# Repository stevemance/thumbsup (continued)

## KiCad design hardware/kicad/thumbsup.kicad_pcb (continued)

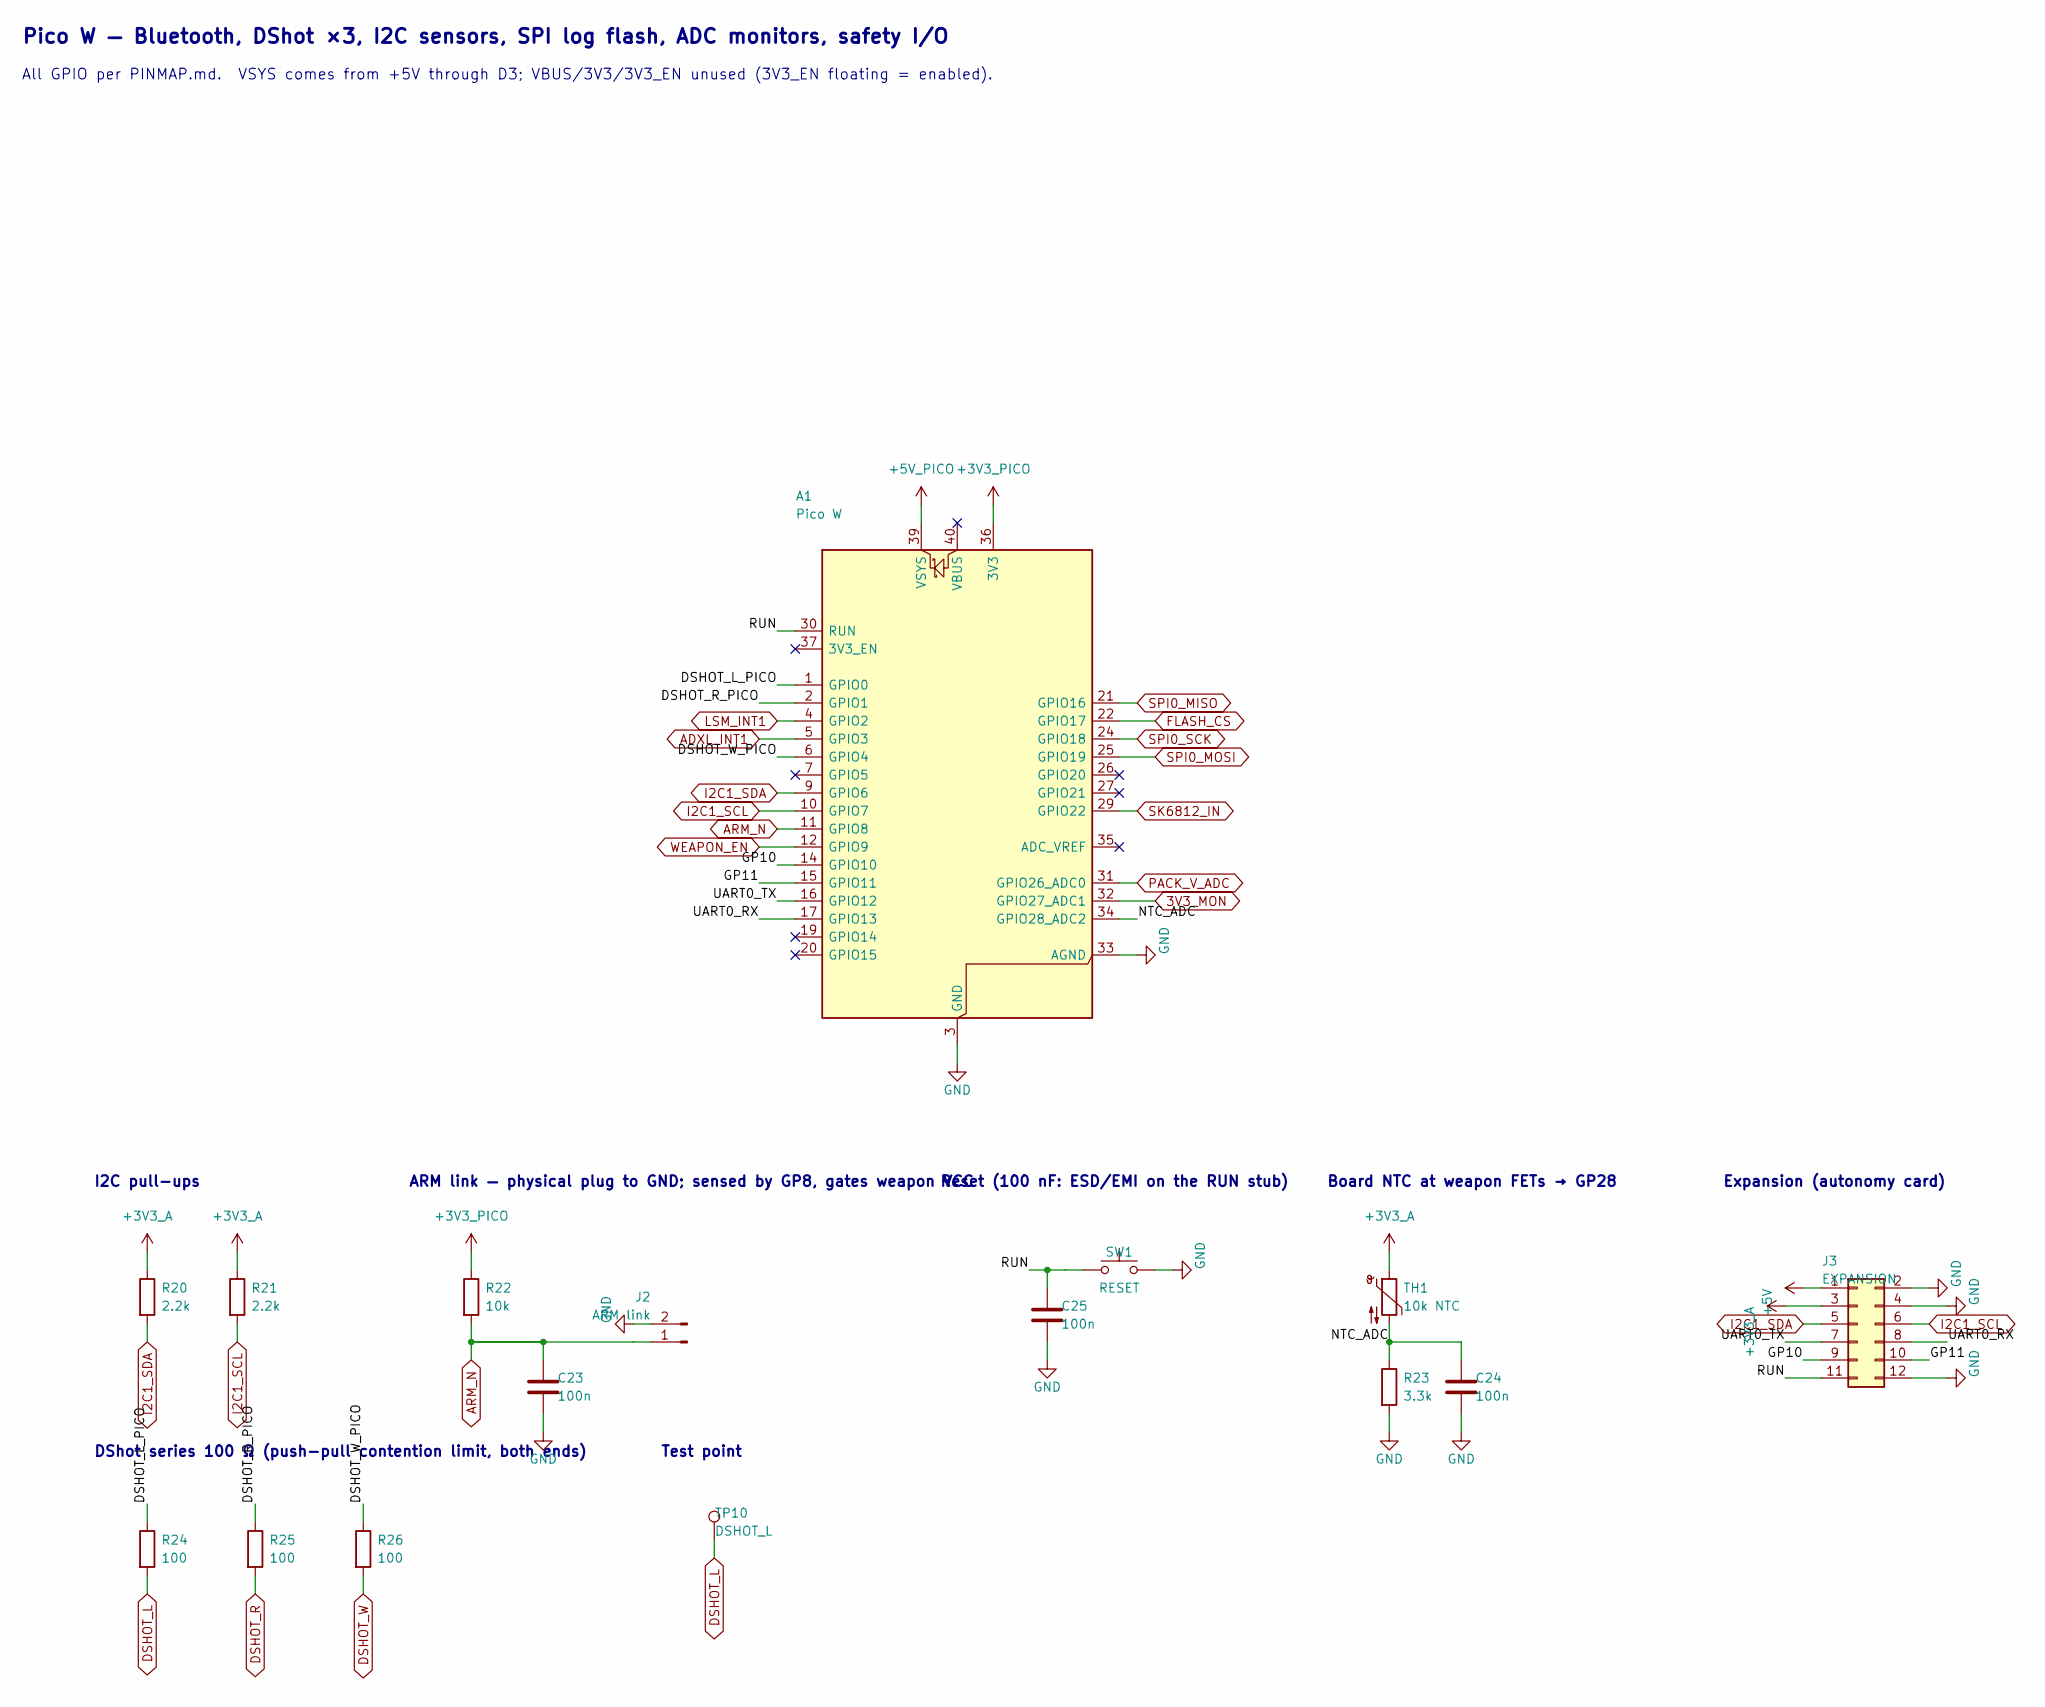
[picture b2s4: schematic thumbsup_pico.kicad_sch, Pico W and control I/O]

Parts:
A1: Pico W; RaspberryPi_Pico_W_SMD_HandSolder
C23, C24, C25: 100n; C_0402_1005Metric; LCSC C1525
J2: ARM link; PinHeader_1x02_P2.54mm_Vertical
J3: EXPANSION; PinHeader_2x06_P2.54mm_Vertical
R20, R21: 2.2k; R_0402_1005Metric; LCSC C25879
R22: 10k; R_0402_1005Metric; LCSC C25744
R23: 3.3k; R_0402_1005Metric; LCSC C25890
R24, R25, R26: 100; R_0402_1005Metric; LCSC C25076
SW1: RESET; SW_Push_1P1T_XKB_TS-1187A; LCSC C318884
TH1: 10k NTC; R_0603_1608Metric; LCSC C13564
TP10: DSHOT_L; TestPoint_Pad_D1.5mm

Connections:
3V3_MON: A1.32 (GPIO27_ADC1); also elsewhere on the board
+3V3_A: J3.3, R20.1, R21.1, TH1.1; also elsewhere on the board
+3V3_PICO: A1.36 (3V3), R22.1
+5V: J3.1; also elsewhere on the board
+5V_PICO: A1.39 (VSYS); also elsewhere on the board
/Pico W and control I/O/DSHOT_L_PICO: A1.1 (GPIO0), R24.1
/Pico W and control I/O/DSHOT_R_PICO: A1.2 (GPIO1), R25.1
/Pico W and control I/O/DSHOT_W_PICO: A1.6 (GPIO4), R26.1
/Pico W and control I/O/GP10: A1.14 (GPIO10), J3.9
/Pico W and control I/O/GP11: A1.15 (GPIO11), J3.10
/Pico W and control I/O/NTC_ADC: A1.34 (GPIO28_ADC2), C24.1, R23.1, TH1.2
/Pico W and control I/O/RUN: A1.30 (RUN), C25.1, J3.11, SW1.1
/Pico W and control I/O/UART0_RX: A1.17 (GPIO13), J3.8
/Pico W and control I/O/UART0_TX: A1.16 (GPIO12), J3.7
ADXL_INT1: A1.5 (GPIO3); also elsewhere on the board
ARM_N: A1.11 (GPIO8), C23.1, J2.1, R22.2; also elsewhere on the board
DSHOT_L: R24.2, TP10.1; also elsewhere on the board
DSHOT_R: R25.2; also elsewhere on the board
DSHOT_W: R26.2; also elsewhere on the board
FLASH_CS: A1.22 (GPIO17); also elsewhere on the board
GND: A1.3 (GND), A1.8 (GND), A1.13 (GND), A1.18 (GND), A1.23 (GND), A1.28 (GND), A1.33 (AGND), A1.38 (GND), C23.2, C24.2, C25.2, J2.2, J3.2, J3.4, J3.12, R23.2, SW1.2; also elsewhere on the board
I2C1_SCL: A1.10 (GPIO7), J3.6, R21.2; also elsewhere on the board
I2C1_SDA: A1.9 (GPIO6), J3.5, R20.2; also elsewhere on the board
LSM_INT1: A1.4 (GPIO2); also elsewhere on the board
PACK_V_ADC: A1.31 (GPIO26_ADC0); also elsewhere on the board
SK6812_IN: A1.29 (GPIO22); also elsewhere on the board
SPI0_MISO: A1.21 (GPIO16); also elsewhere on the board
SPI0_MOSI: A1.25 (GPIO19); also elsewhere on the board
SPI0_SCK: A1.24 (GPIO18); also elsewhere on the board
WEAPON_EN: A1.12 (GPIO9); also elsewhere on the board

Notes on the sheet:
Pico W — Bluetooth, DShot ×3, I2C sensors, SPI log flash, ADC monitors, safety I/O
All GPIO per PINMAP.md. VSYS comes from +5V through D3; VBUS/3V3/3V3_EN unused (3V3_EN floating = enabled).
I2C pull-ups
ARM link — physical plug to GND; sensed by GP8, gates weapon VCC
Reset (100 nF: ESD/EMI on the RUN stub)
DShot series 100 Ω (push-pull contention limit, both ends)
Test point
Board NTC at weapon FETs → GP28
Expansion (autonomy card)

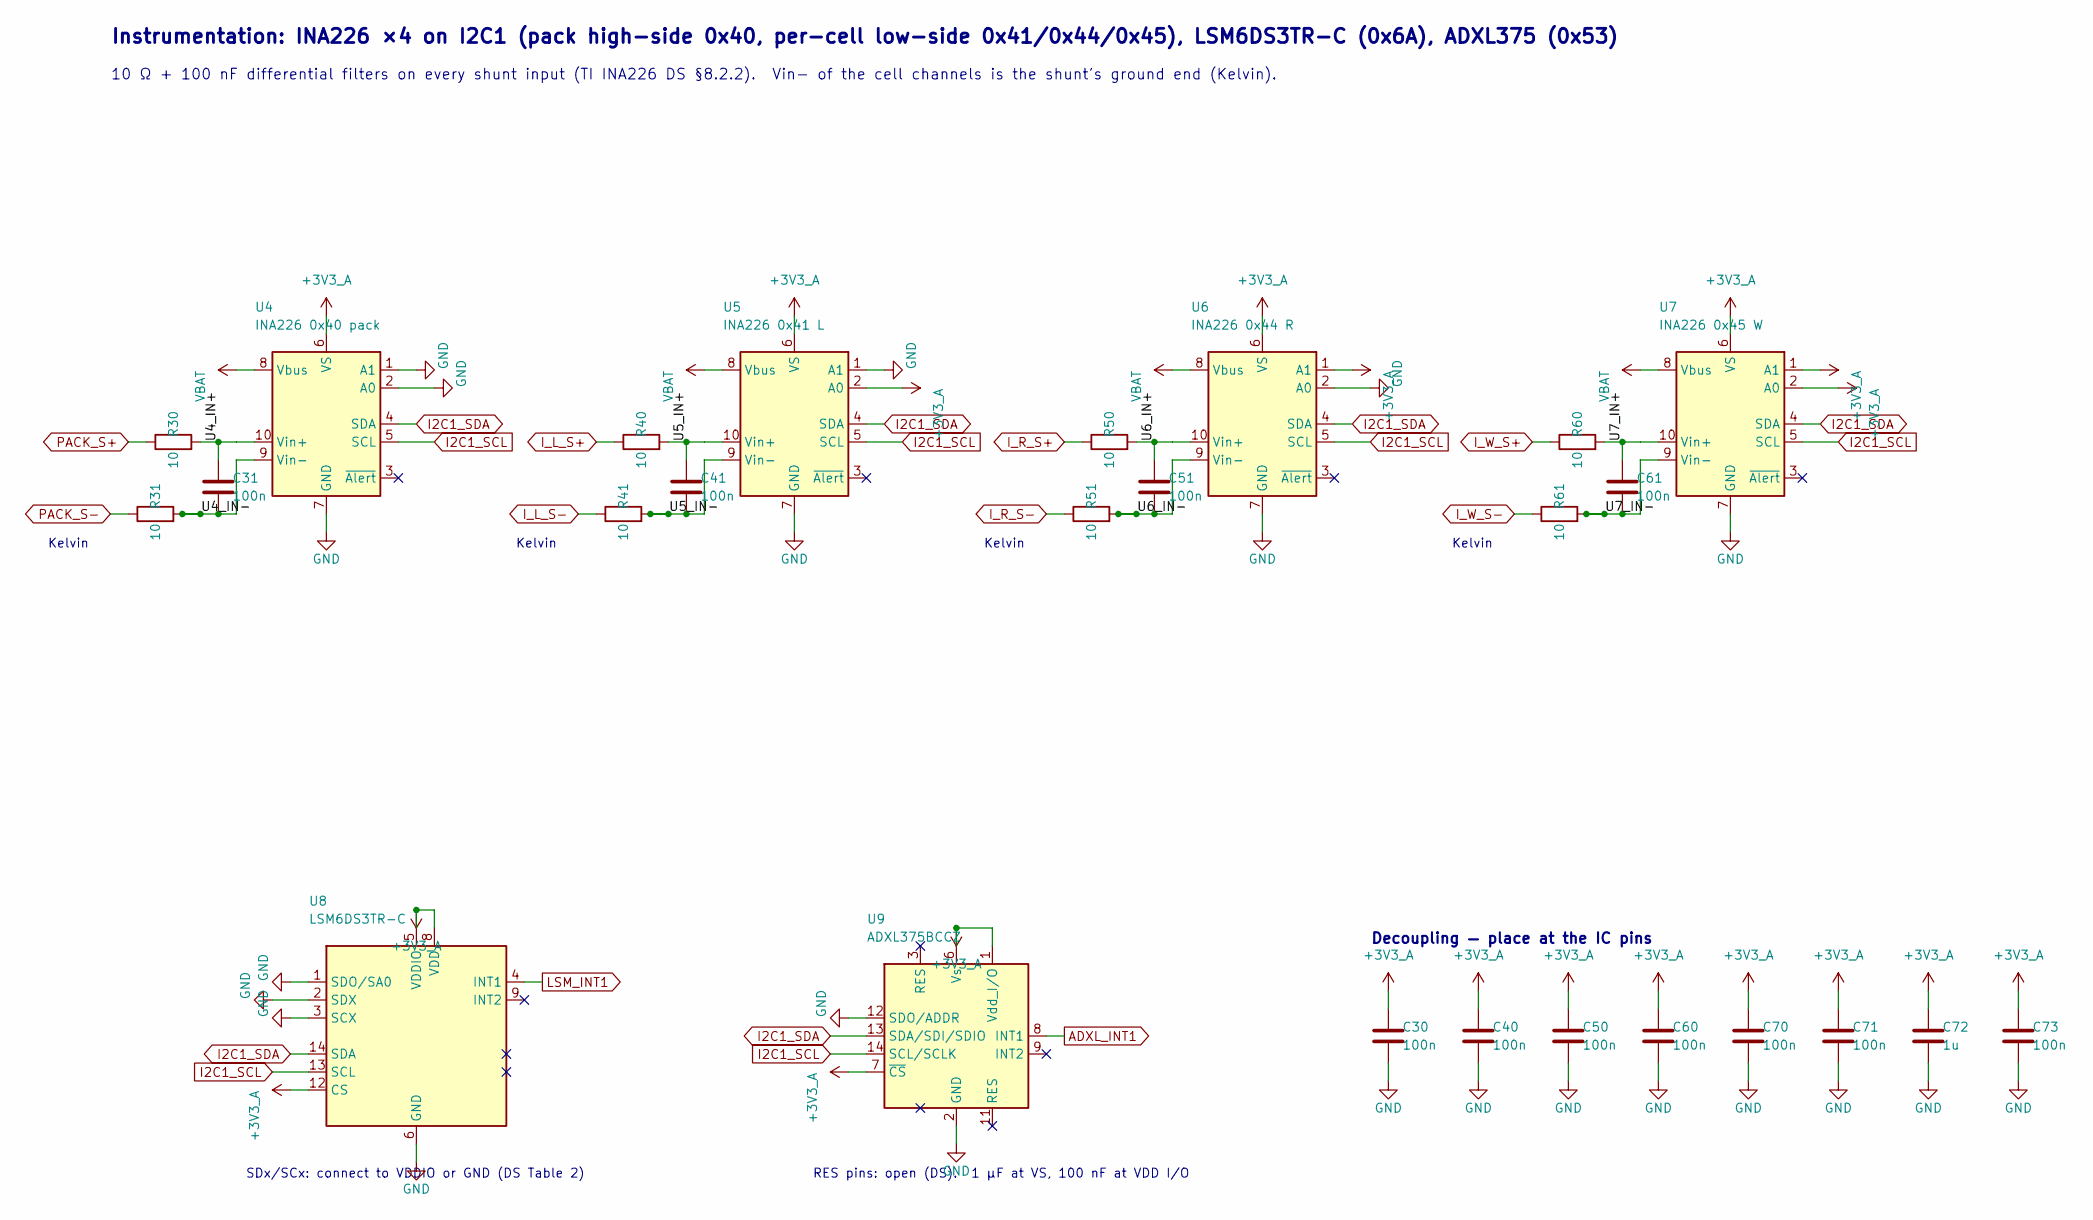
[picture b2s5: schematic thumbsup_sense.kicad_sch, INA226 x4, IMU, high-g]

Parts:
C30, C31, C40, C41, C50, C51, C60, C61, C70, C71, C73: 100n; C_0402_1005Metric; LCSC C1525
C72: 1u; C_0402_1005Metric; LCSC C52923
R30, R31, R40, R41, R50, R51, R60, R61: 10; R_0402_1005Metric; LCSC C25077
U4: INA226 0x40 pack; MSOP-10_3x3mm_P0.5mm; LCSC C49851
U5: INA226 0x41 L; MSOP-10_3x3mm_P0.5mm; LCSC C49851
U6: INA226 0x44 R; MSOP-10_3x3mm_P0.5mm; LCSC C49851
U7: INA226 0x45 W; MSOP-10_3x3mm_P0.5mm; LCSC C49851
U8: LSM6DS3TR-C; LGA-14_3x2.5mm_P0.5mm_LayoutBorder3x4y; LCSC C967633
U9: ADXL375BCCZ; LGA-14_3x5mm_P0.8mm_LayoutBorder1x6y; LCSC C579466

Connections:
+3V3_A: C30.1, C40.1, C50.1, C60.1, C70.1, C71.1, C72.1, C73.1, U4.6 (VS), U5.2 (A0), U5.6 (VS), U6.1 (A1), U6.6 (VS), U7.1 (A1), U7.2 (A0), U7.6 (VS), U8.5 (VDDIO), U8.8 (VDD), U8.12 (CS), U9.1 (Vdd_I/O), U9.6 (Vs), U9.7 (~CS); also elsewhere on the board
/INA226 x4, IMU, high-g/U4_IN+: C31.1, R30.2, U4.10 (Vin+)
/INA226 x4, IMU, high-g/U4_IN-: C31.2, R31.2, U4.9 (Vin-)
/INA226 x4, IMU, high-g/U5_IN+: C41.1, R40.2, U5.10 (Vin+)
/INA226 x4, IMU, high-g/U5_IN-: C41.2, R41.2, U5.9 (Vin-)
/INA226 x4, IMU, high-g/U6_IN+: C51.1, R50.2, U6.10 (Vin+)
/INA226 x4, IMU, high-g/U6_IN-: C51.2, R51.2, U6.9 (Vin-)
/INA226 x4, IMU, high-g/U7_IN+: C61.1, R60.2, U7.10 (Vin+)
/INA226 x4, IMU, high-g/U7_IN-: C61.2, R61.2, U7.9 (Vin-)
ADXL_INT1: U9.8 (INT1); also elsewhere on the board
GND: C30.2, C40.2, C50.2, C60.2, C70.2, C71.2, C72.2, C73.2, U4.1 (A1), U4.2 (A0), U4.7 (GND), U5.1 (A1), U5.7 (GND), U6.2 (A0), U6.7 (GND), U7.7 (GND), U8.1 (SDO/SA0), U8.2 (SDX), U8.3 (SCX), U8.6 (GND), U8.7 (GND), U9.2 (GND), U9.4 (GND), U9.5 (GND), U9.12 (SDO/ADDR); also elsewhere on the board
I2C1_SCL: U4.5 (SCL), U5.5 (SCL), U6.5 (SCL), U7.5 (SCL), U8.13 (SCL), U9.14 (SCL/SCLK); also elsewhere on the board
I2C1_SDA: U4.4 (SDA), U5.4 (SDA), U6.4 (SDA), U7.4 (SDA), U8.14 (SDA), U9.13 (SDA/SDI/SDIO); also elsewhere on the board
I_L_S+: R40.1; also elsewhere on the board
I_L_S-: R41.1; also elsewhere on the board
I_R_S+: R50.1; also elsewhere on the board
I_R_S-: R51.1; also elsewhere on the board
I_W_S+: R60.1; also elsewhere on the board
I_W_S-: R61.1; also elsewhere on the board
LSM_INT1: U8.4 (INT1); also elsewhere on the board
PACK_S+: R30.1; also elsewhere on the board
PACK_S-: R31.1; also elsewhere on the board
VBAT: U4.8 (Vbus), U5.8 (Vbus), U6.8 (Vbus), U7.8 (Vbus); also elsewhere on the board

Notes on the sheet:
Instrumentation: INA226 ×4 on I2C1 (pack high-side 0x40, per-cell low-side 0x41/0x44/0x45), LSM6DS3TR-C (0x6A), ADXL375 (0x53)
10 Ω + 100 nF differential filters on every shunt input (TI INA226 DS §8.2.2). Vin− of the cell channels is the shunt's ground end (Kelvin).
Kelvin
SDx/SCx: connect to VDDIO or GND (DS Table 2)
RES pins: open (DS). 1 µF at VS, 100 nF at VDD I/O
Decoupling — place at the IC pins

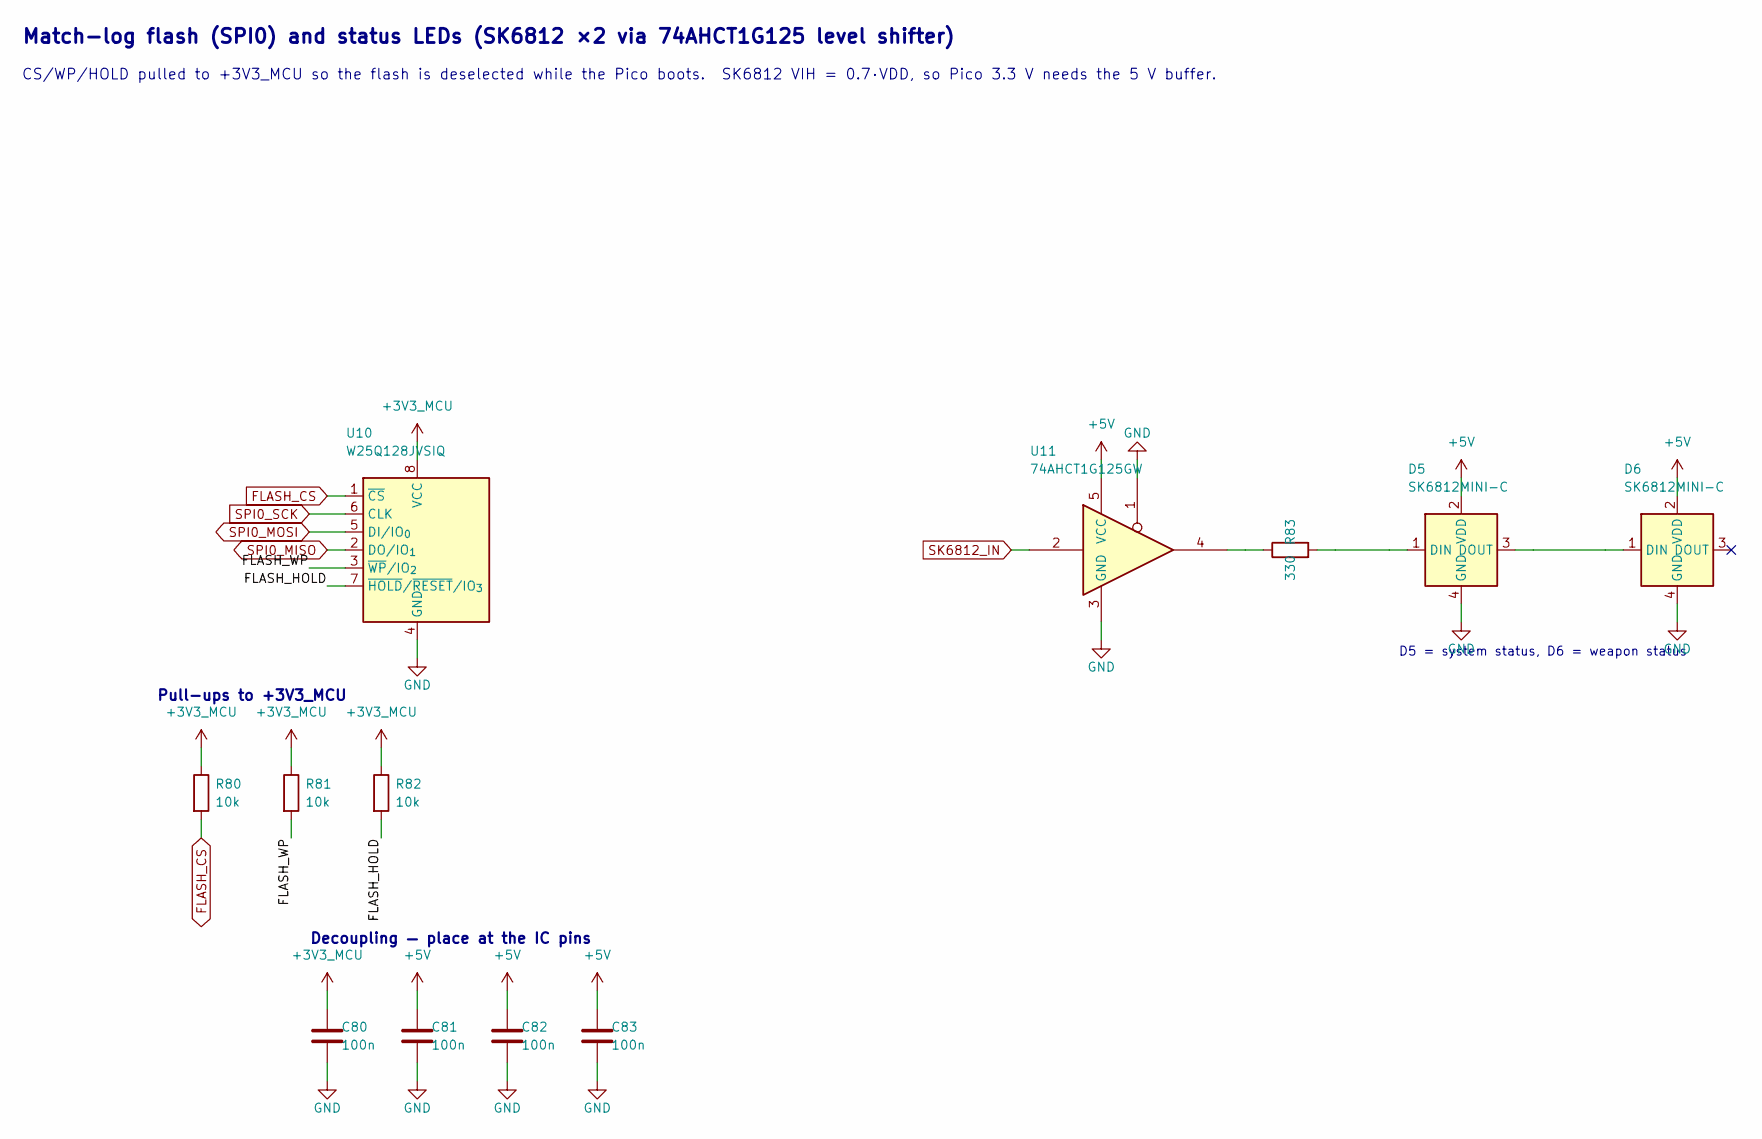
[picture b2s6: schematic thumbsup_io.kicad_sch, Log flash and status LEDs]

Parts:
C80, C81, C82, C83: 100n; C_0402_1005Metric; LCSC C1525
D5, D6: SK6812MINI-C; LED_SK6812MINI_PLCC4_3.5x3.5mm_P1.75mm; LCSC C7423117
R80, R81, R82: 10k; R_0402_1005Metric; LCSC C25744
R83: 330; R_0402_1005Metric; LCSC C25104
U10: W25Q128JVSIQ; SOIC-8_5.3x5.3mm_P1.27mm; LCSC C97521
U11: 74AHCT1G125GW; SOT-353_SC-70-5; LCSC C52953352

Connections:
+3V3_MCU: C80.1, R80.1, R81.1, R82.1, U10.8 (VCC); also elsewhere on the board
+5V: C81.1, C82.1, C83.1, D5.2 (VDD), D6.2 (VDD), U11.5 (VCC); also elsewhere on the board
/Log flash and status LEDs/FLASH_HOLD: R82.2, U10.7 (~HOLD/~RESET/IO_{3})
/Log flash and status LEDs/FLASH_WP: R81.2, U10.3 (~WP/IO_{2})
FLASH_CS: R80.2, U10.1 (~CS); also elsewhere on the board
GND: C80.2, C81.2, C82.2, C83.2, D5.4 (GND), D6.4 (GND), U10.4 (GND), U11.1, U11.3 (GND); also elsewhere on the board
unnamed: D5.1 (DIN), R83.2
unnamed: D5.3 (DOUT), D6.1 (DIN)
unnamed: R83.1, U11.4
SK6812_IN: U11.2; also elsewhere on the board
SPI0_MISO: U10.2 (DO/IO_{1}); also elsewhere on the board
SPI0_MOSI: U10.5 (DI/IO_{0}); also elsewhere on the board
SPI0_SCK: U10.6 (CLK); also elsewhere on the board

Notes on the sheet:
Match-log flash (SPI0) and status LEDs (SK6812 ×2 via 74AHCT1G125 level shifter)
CS/WP/HOLD pulled to +3V3_MCU so the flash is deselected while the Pico boots. SK6812 VIH = 0.7·VDD, so Pico 3.3 V needs the 5 V buffer.
Pull-ups to +3V3_MCU
D5 = system status, D6 = weapon status
Decoupling — place at the IC pins

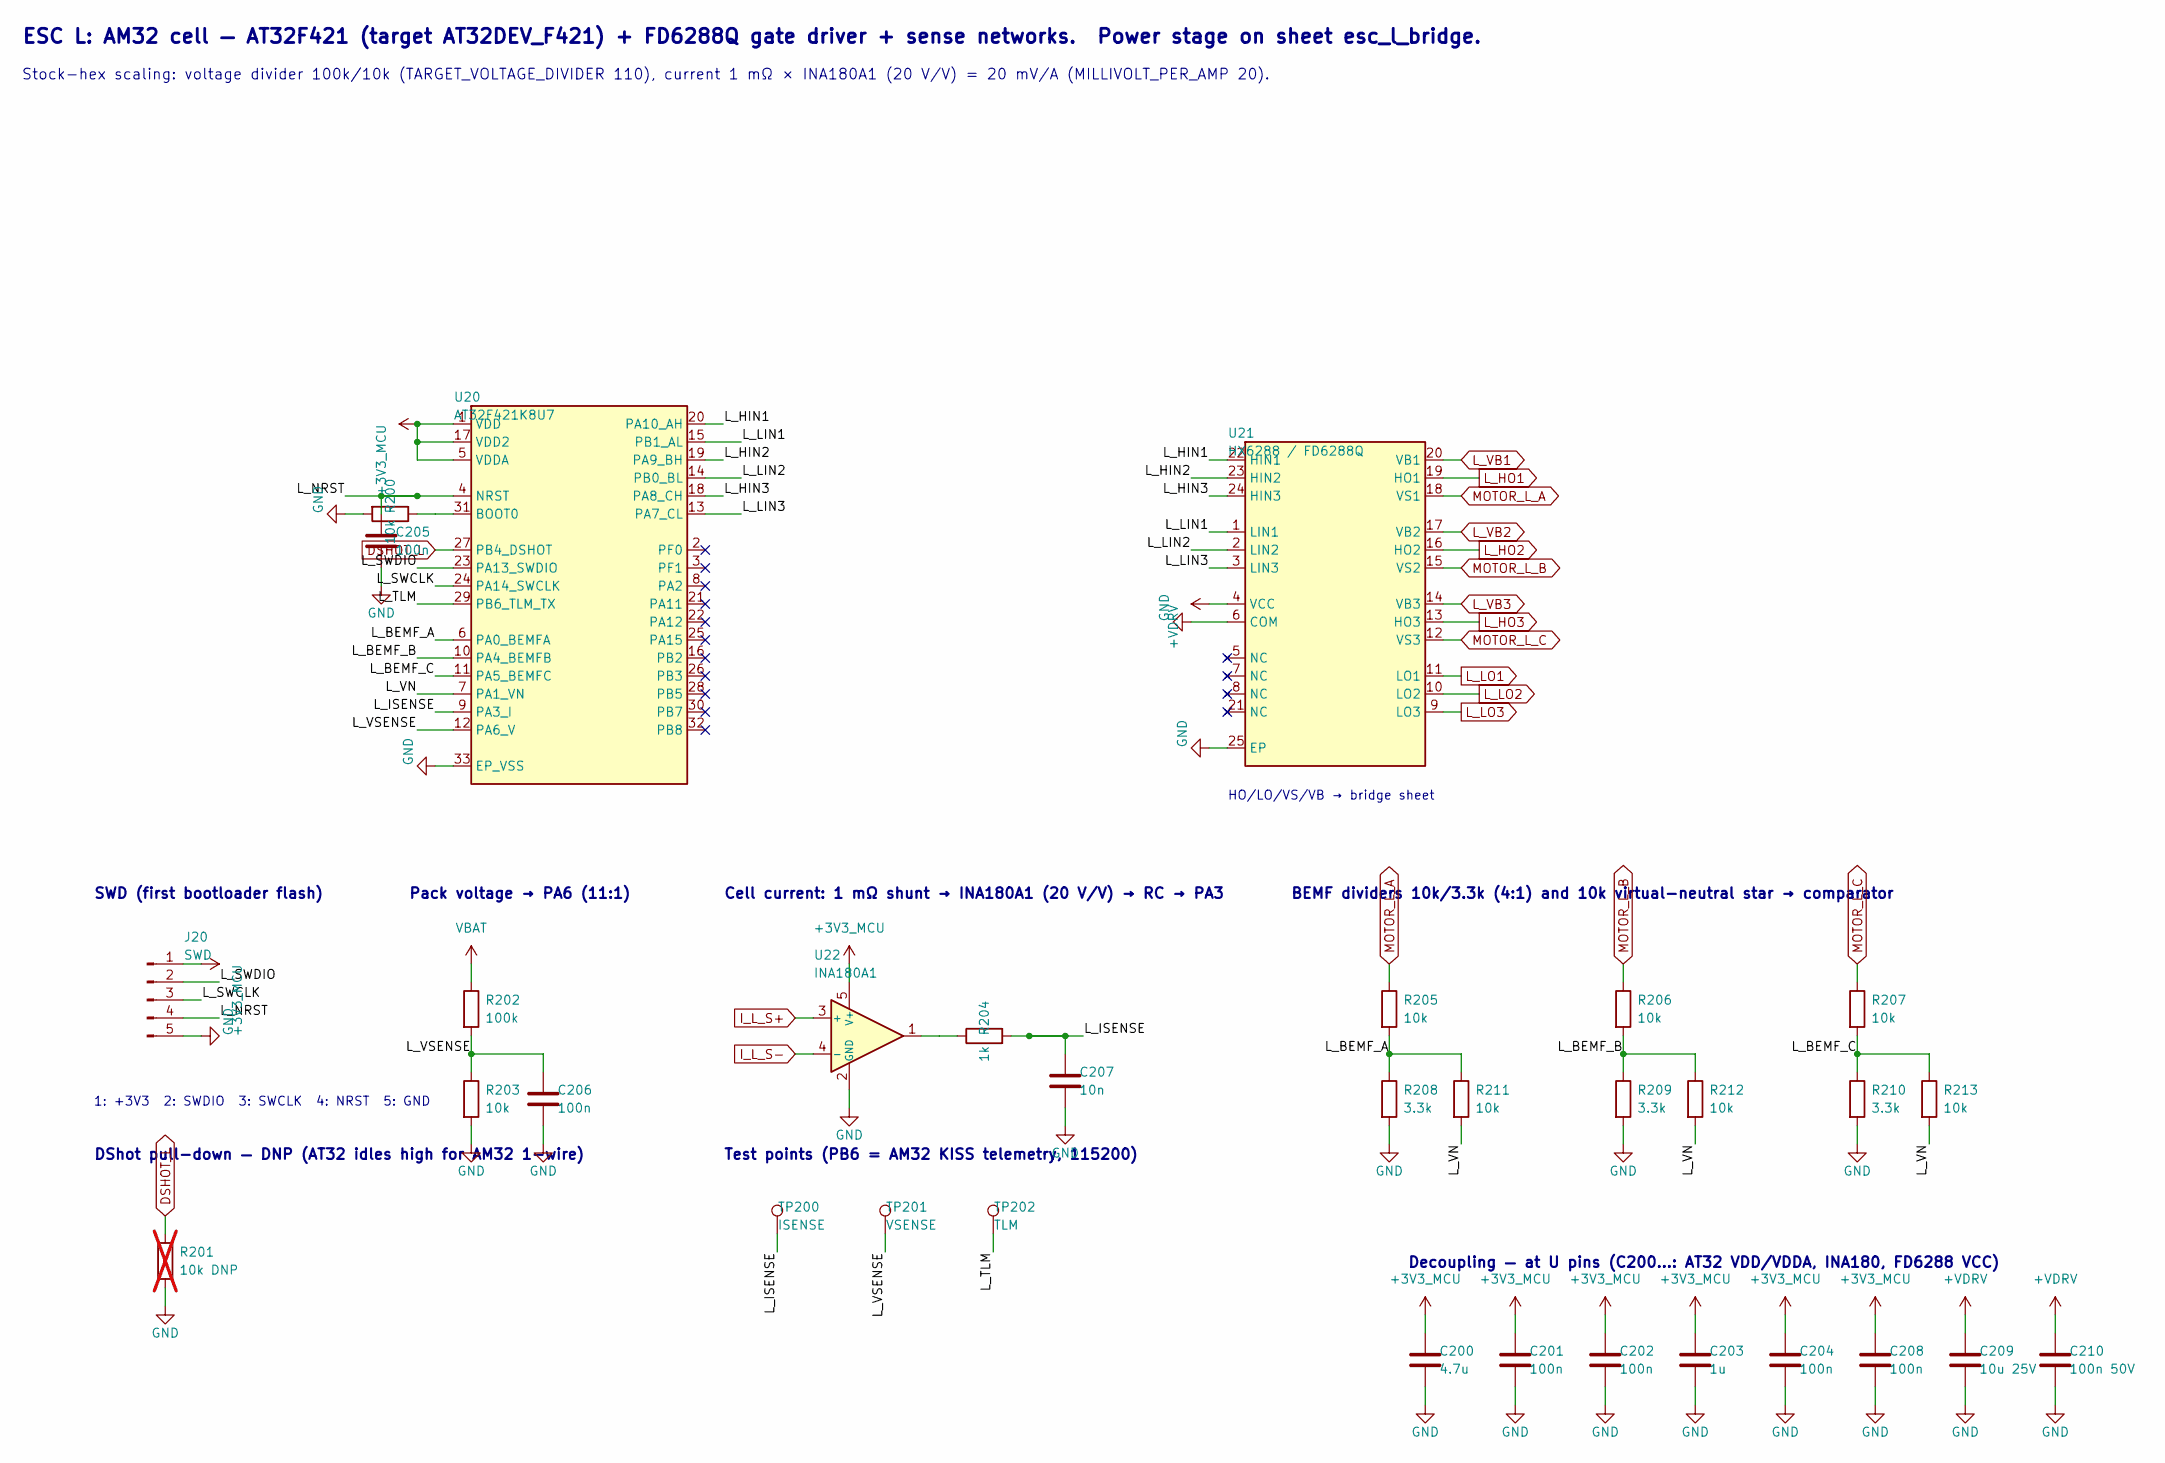
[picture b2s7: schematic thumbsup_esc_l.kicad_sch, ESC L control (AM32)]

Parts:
C200: 4.7u; C_0603_1608Metric; LCSC C19666
C201, C202, C204, C205, C206, C208: 100n; C_0402_1005Metric; LCSC C1525
C203: 1u; C_0402_1005Metric; LCSC C52923
C207: 10n; C_0402_1005Metric; LCSC C15195
C209: 10u 25V; C_0805_2012Metric; LCSC C15850
C210: 100n 50V; C_0603_1608Metric; LCSC C14663
J20: SWD; SWD_1x05_P1.27mm_Pads
R200, R203, R205, R206, R207, R211, R212, R213: 10k; R_0402_1005Metric; LCSC C25744
R201: 10k DNP; R_0402_1005Metric; LCSC C25744; not fitted
R202: 100k; R_0402_1005Metric; LCSC C25741
R204: 1k; R_0402_1005Metric; LCSC C11702
R208, R209, R210: 3.3k; R_0402_1005Metric; LCSC C25890
TP200: ISENSE; TestPoint_Pad_D1.5mm
TP201: VSENSE; TestPoint_Pad_D1.5mm
TP202: TLM; TestPoint_Pad_D1.5mm
U20: AT32F421K8U7; QFN-32-1EP_5x5mm_P0.5mm_EP3.3x3.3mm; LCSC C2965611
U21: HX6288 / FD6288Q; QFN-24-1EP_4x4mm_P0.5mm_EP2.7x2.7mm; LCSC C54423134
U22: INA180A1; SOT-23-5; LCSC C122228

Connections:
+3V3_MCU: C200.1, C201.1, C202.1, C203.1, C204.1, C208.1, J20.1, U20.1 (VDD), U20.5 (VDDA), U20.17 (VDD2), U22.5 (V+); also elsewhere on the board
+VDRV: C209.1, C210.1, U21.4 (VCC); also elsewhere on the board
/ESC L control (AM32)/L_BEMF_A: R205.2, R208.1, R211.1, U20.6 (PA0_BEMFA)
/ESC L control (AM32)/L_BEMF_B: R206.2, R209.1, R212.1, U20.10 (PA4_BEMFB)
/ESC L control (AM32)/L_BEMF_C: R207.2, R210.1, R213.1, U20.11 (PA5_BEMFC)
/ESC L control (AM32)/L_HIN1: U20.20 (PA10_AH), U21.22 (HIN1)
/ESC L control (AM32)/L_HIN2: U20.19 (PA9_BH), U21.23 (HIN2)
/ESC L control (AM32)/L_HIN3: U20.18 (PA8_CH), U21.24 (HIN3)
/ESC L control (AM32)/L_ISENSE: C207.1, R204.2, TP200.1, U20.9 (PA3_I)
/ESC L control (AM32)/L_LIN1: U20.15 (PB1_AL), U21.1 (LIN1)
/ESC L control (AM32)/L_LIN2: U20.14 (PB0_BL), U21.2 (LIN2)
/ESC L control (AM32)/L_LIN3: U20.13 (PA7_CL), U21.3 (LIN3)
/ESC L control (AM32)/L_NRST: C205.1, J20.4, U20.4 (NRST)
/ESC L control (AM32)/L_SWCLK: J20.3, U20.24 (PA14_SWCLK)
/ESC L control (AM32)/L_SWDIO: J20.2, U20.23 (PA13_SWDIO)
/ESC L control (AM32)/L_TLM: TP202.1, U20.29 (PB6_TLM_TX)
/ESC L control (AM32)/L_VN: R211.2, R212.2, R213.2, U20.7 (PA1_VN)
/ESC L control (AM32)/L_VSENSE: C206.1, R202.2, R203.1, TP201.1, U20.12 (PA6_V)
DSHOT_L: R201.1, U20.27 (PB4_DSHOT); also elsewhere on the board
GND: C200.2, C201.2, C202.2, C203.2, C204.2, C205.2, C206.2, C207.2, C208.2, C209.2, C210.2, J20.5, R200.2, R201.2, R203.2, R208.2, R209.2, R210.2, U20.33 (EP_VSS), U21.6 (COM), U21.25 (EP), U22.2 (GND); also elsewhere on the board
I_L_S+: U22.3 (+); also elsewhere on the board
I_L_S-: U22.4 (-); also elsewhere on the board
L_HO1: U21.19 (HO1); also elsewhere on the board
L_HO2: U21.16 (HO2); also elsewhere on the board
L_HO3: U21.13 (HO3); also elsewhere on the board
L_LO1: U21.11 (LO1); also elsewhere on the board
L_LO2: U21.10 (LO2); also elsewhere on the board
L_LO3: U21.9 (LO3); also elsewhere on the board
L_VB1: U21.20 (VB1); also elsewhere on the board
L_VB2: U21.17 (VB2); also elsewhere on the board
L_VB3: U21.14 (VB3); also elsewhere on the board
MOTOR_L_A: R205.1, U21.18 (VS1); also elsewhere on the board
MOTOR_L_B: R206.1, U21.15 (VS2); also elsewhere on the board
MOTOR_L_C: R207.1, U21.12 (VS3); also elsewhere on the board
unnamed: R204.1, U22.1
unnamed: R200.1, U20.31 (BOOT0)
VBAT: R202.1; also elsewhere on the board

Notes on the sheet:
ESC L: AM32 cell — AT32F421 (target AT32DEV_F421) + FD6288Q gate driver + sense networks. Power stage on sheet esc_l_bridge.
Stock-hex scaling: voltage divider 100k/10k (TARGET_VOLTAGE_DIVIDER 110), current 1 mΩ × INA180A1 (20 V/V) = 20 mV/A (MILLIVOLT_PER_AMP 20).
HO/LO/VS/VB → bridge sheet
SWD (first bootloader flash)
1: +3V3 2: SWDIO 3: SWCLK 4: NRST 5: GND
DShot pull-down — DNP (AT32 idles high for AM32 1-wire)
Pack voltage → PA6 (11:1)
Cell current: 1 mΩ shunt → INA180A1 (20 V/V) → RC → PA3
BEMF dividers 10k/3.3k (4:1) and 10k virtual-neutral star → comparator
Decoupling — at U pins (C200…: AT32 VDD/VDDA, INA180, FD6288 VCC)
Test points (PB6 = AM32 KISS telemetry, 115200)

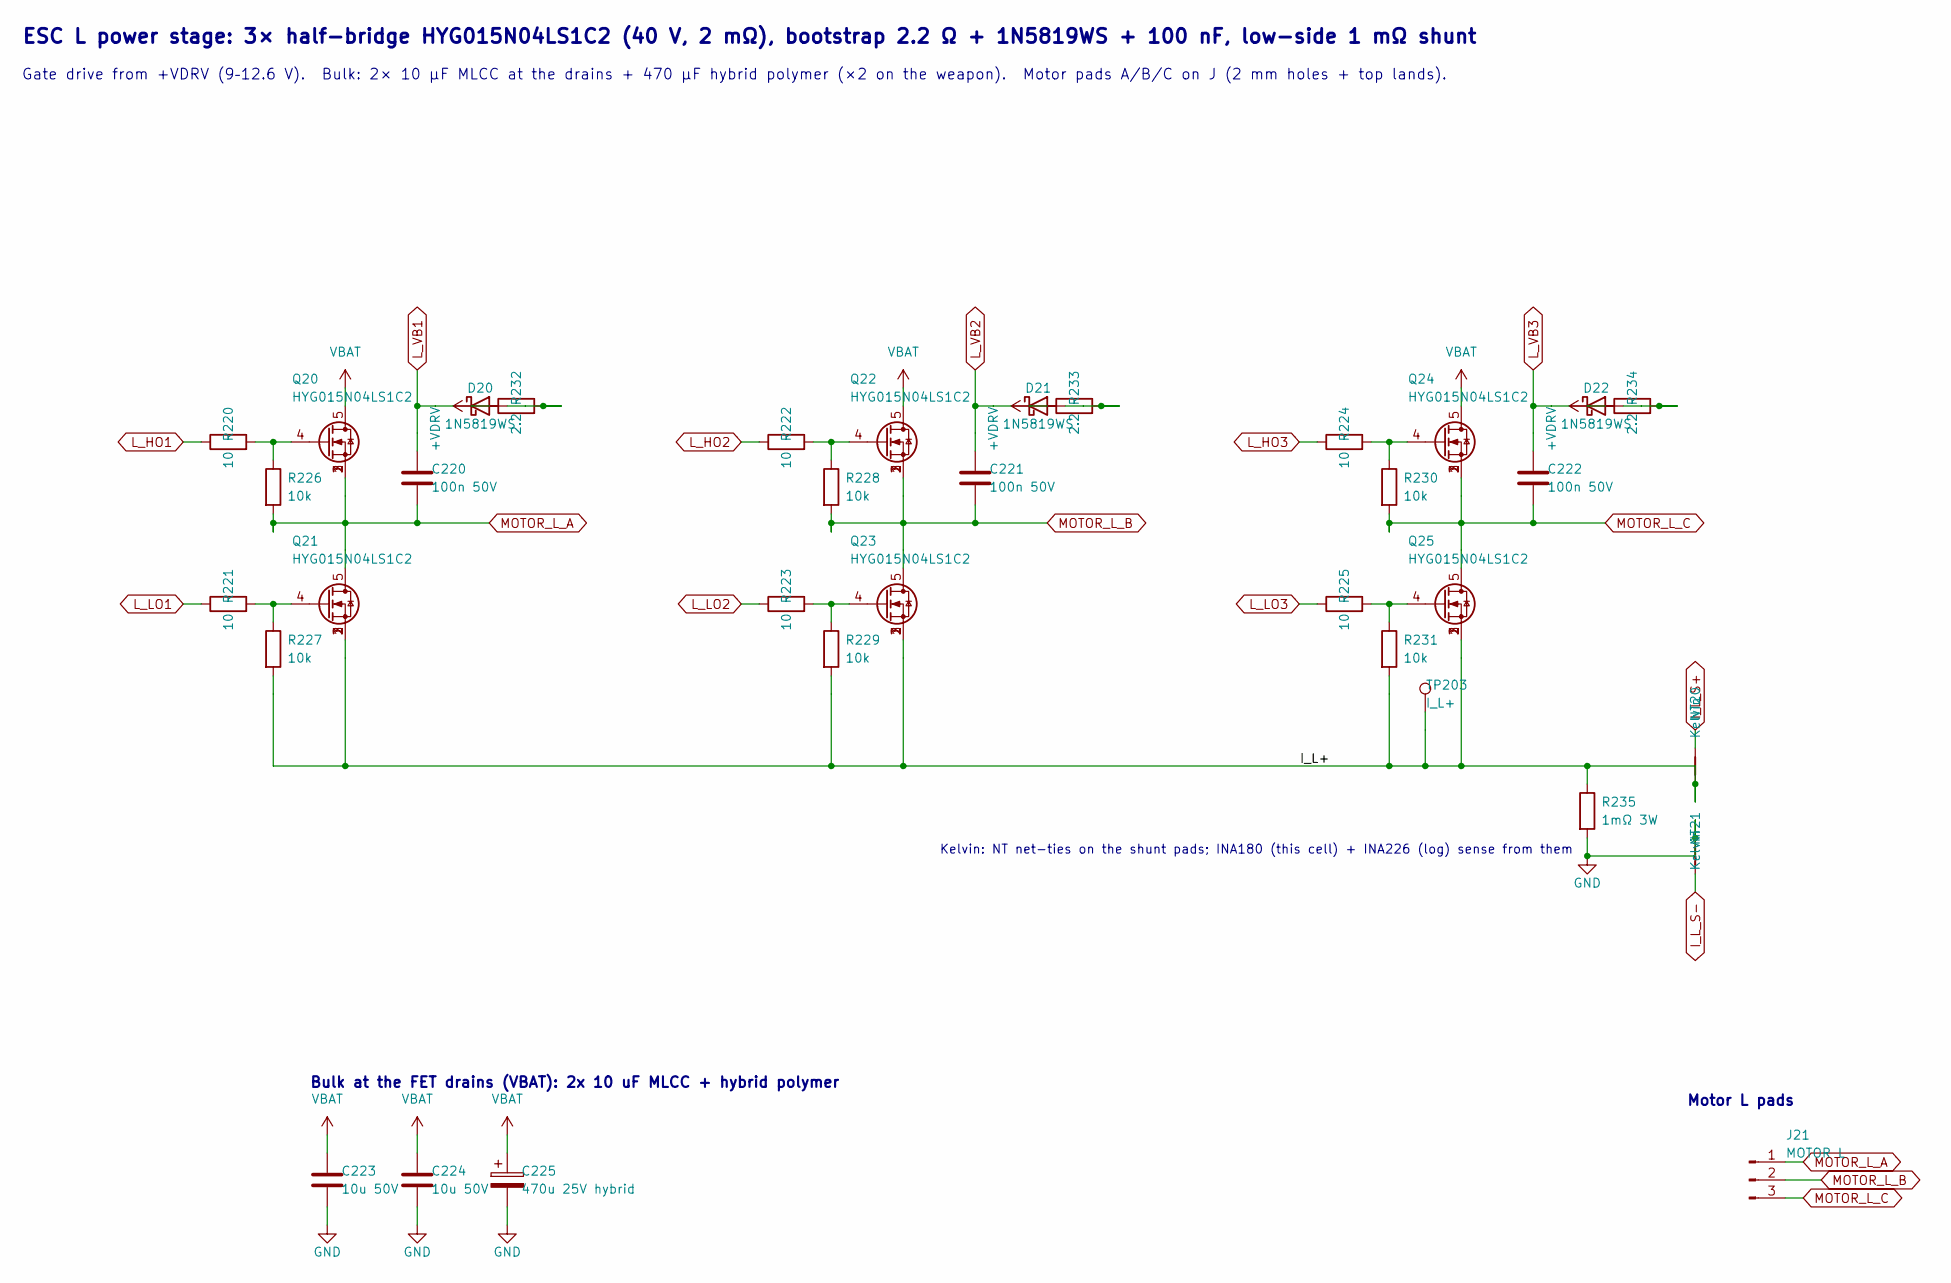
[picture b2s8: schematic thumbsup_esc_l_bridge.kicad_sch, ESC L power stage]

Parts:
C220, C221, C222: 100n 50V; C_0603_1608Metric; LCSC C14663
C223, C224: 10u 50V; C_1206_3216Metric; LCSC C13585
C225: 470u 25V hybrid; CP_Elec_10x10.5; LCSC C242138
D20, D21, D22: 1N5819WS; D_SOD-323; LCSC C191023
J21: MOTOR L; MotorHoles_1x03_P5.90mm
NT20, NT21: Kelvin; NetTie-2_Kelvin_0.4mm
Q20, Q21, Q22, Q23, Q24, Q25: HYG015N04LS1C2; PQFN-8-EP_6x5mm_P1.27mm_Generic; LCSC C2874970
R220, R221, R222, R223, R224, R225: 10; R_0402_1005Metric; LCSC C25077
R226, R227, R228, R229, R230, R231: 10k; R_0402_1005Metric; LCSC C25744
R232, R233, R234: 2.2; R_0603_1608Metric; LCSC C22939
R235: 1mΩ 3W; R_2512_Shunt_Kelvin; LCSC C46961745
TP203: I_L+; TestPoint_Pad_D1.5mm

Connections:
+VDRV: R232.1, R233.1, R234.1; also elsewhere on the board
/ESC L power stage/I_L+: NT20.1, Q21.1 (S), Q21.2 (S), Q21.3 (S), Q23.1 (S), Q23.2 (S), Q23.3 (S), Q25.1 (S), Q25.2 (S), Q25.3 (S), R227.2, R229.2, R231.2, R235.1, TP203.1
GND: C223.2, C224.2, C225.2, NT21.1, R235.2; also elsewhere on the board
I_L_S+: NT20.2; also elsewhere on the board
I_L_S-: NT21.2; also elsewhere on the board
L_HO1: R220.1; also elsewhere on the board
L_HO2: R222.1; also elsewhere on the board
L_HO3: R224.1; also elsewhere on the board
L_LO1: R221.1; also elsewhere on the board
L_LO2: R223.1; also elsewhere on the board
L_LO3: R225.1; also elsewhere on the board
L_VB1: C220.1, D20.1 (K); also elsewhere on the board
L_VB2: C221.1, D21.1 (K); also elsewhere on the board
L_VB3: C222.1, D22.1 (K); also elsewhere on the board
MOTOR_L_A: C220.2, J21.1, Q20.1 (S), Q20.2 (S), Q20.3 (S), Q21.5 (D), R226.2; also elsewhere on the board
MOTOR_L_B: C221.2, J21.2, Q22.1 (S), Q22.2 (S), Q22.3 (S), Q23.5 (D), R228.2; also elsewhere on the board
MOTOR_L_C: C222.2, J21.3, Q24.1 (S), Q24.2 (S), Q24.3 (S), Q25.5 (D), R230.2; also elsewhere on the board
unnamed: D20.2 (A), R232.2
unnamed: D21.2 (A), R233.2
unnamed: D22.2 (A), R234.2
unnamed: Q20.4 (G), R220.2, R226.1
unnamed: Q21.4 (G), R221.2, R227.1
unnamed: Q22.4 (G), R222.2, R228.1
unnamed: Q23.4 (G), R223.2, R229.1
unnamed: Q24.4 (G), R224.2, R230.1
unnamed: Q25.4 (G), R225.2, R231.1
VBAT: C223.1, C224.1, C225.1, Q20.5 (D), Q22.5 (D), Q24.5 (D); also elsewhere on the board

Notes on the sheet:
ESC L power stage: 3× half-bridge HYG015N04LS1C2 (40 V, 2 mΩ), bootstrap 2.2 Ω + 1N5819WS + 100 nF, low-side 1 mΩ shunt
Gate drive from +VDRV (9–12.6 V). Bulk: 2× 10 µF MLCC at the drains + 470 µF hybrid polymer (×2 on the weapon). Motor pads A/B/C on J (2 mm holes + top lands).
Kelvin: NT net-ties on the shunt pads; INA180 (this cell) + INA226 (log) sense from them
Bulk at the FET drains (VBAT): 2x 10 uF MLCC + hybrid polymer
Motor L pads
